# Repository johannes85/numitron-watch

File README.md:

Numitron Geekwatch
==============

See: http://www.domestichacks.info/projekte/numitron-geekwatch-armbanduhr/

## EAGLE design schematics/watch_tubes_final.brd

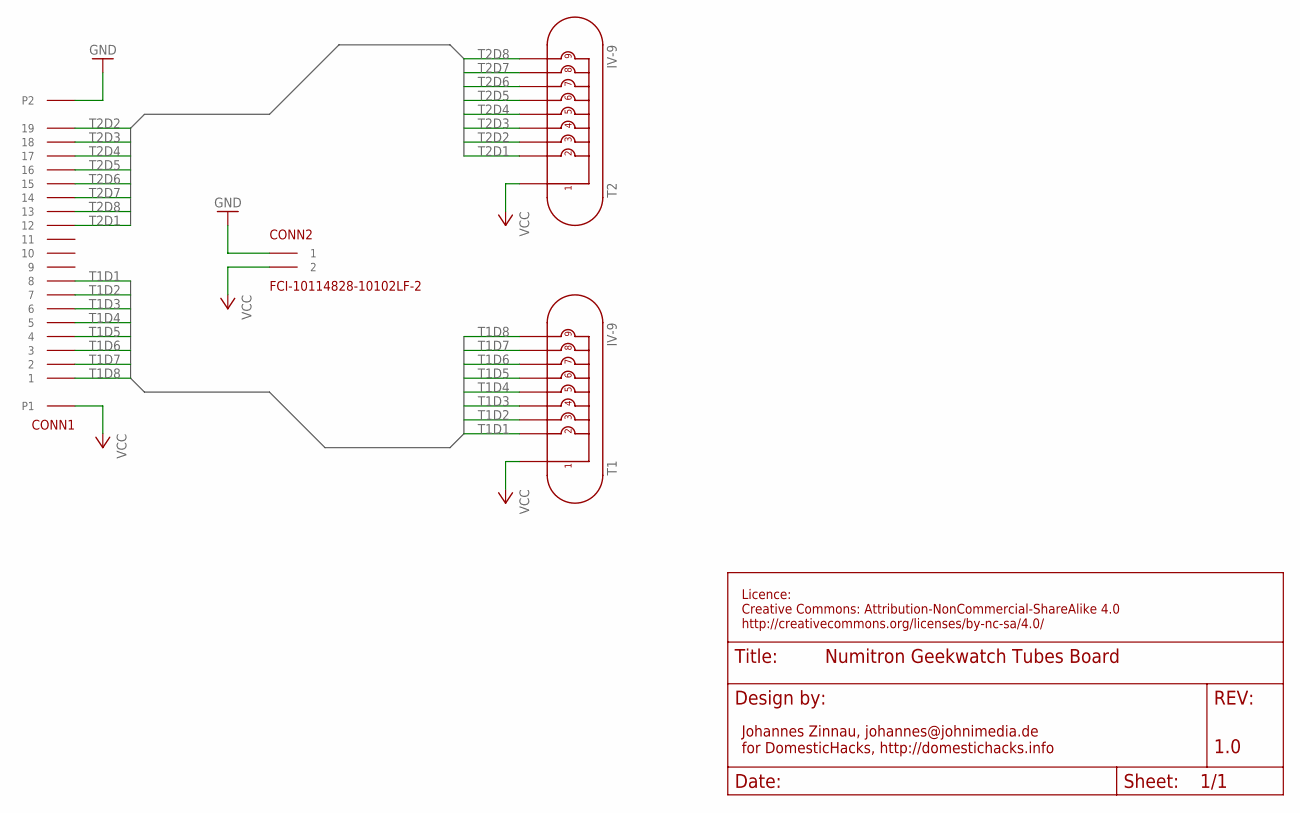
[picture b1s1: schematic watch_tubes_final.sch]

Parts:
CONN1: PCBMOUNT-20SECOND; PCBMOUNT-VERTICAL-20-2
CONN2: FCI-10114828-10102LF-2
T1, T2: IV-9

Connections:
GND: CONN1.P2, CONN2.1
T1D1: CONN1.8, T1.2
T1D2: CONN1.7, T1.3
T1D3: CONN1.6, T1.4
T1D4: CONN1.5, T1.5
T1D5: CONN1.4, T1.6
T1D6: CONN1.3, T1.7
T1D7: CONN1.2, T1.8
T1D8: CONN1.1, T1.9
T2D1: CONN1.12, T2.2
T2D2: CONN1.19, T2.3
T2D3: CONN1.18, T2.4
T2D4: CONN1.17, T2.5
T2D5: CONN1.16, T2.6
T2D6: CONN1.15, T2.7
T2D7: CONN1.14, T2.8
T2D8: CONN1.13, T2.9
VCC: CONN1.P1, CONN2.2, T1.1, T2.1

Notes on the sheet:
Licence: Creative Commons: Attribution-NonCommercial-ShareAlike 4.0 http://creativecommons.org/licenses/by-nc-sa/4.0/
Johannes Zinnau, johannes@johnimedia.de for DomesticHacks, http://domestichacks.info
1.0

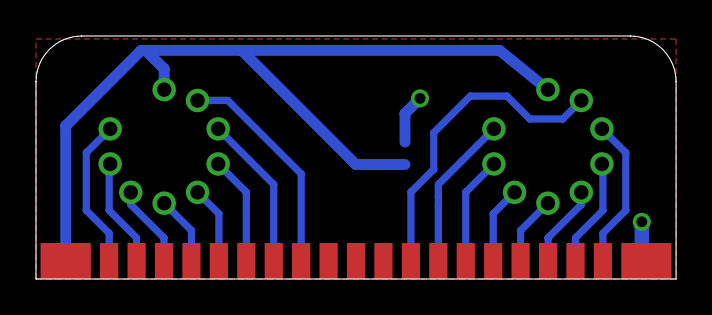
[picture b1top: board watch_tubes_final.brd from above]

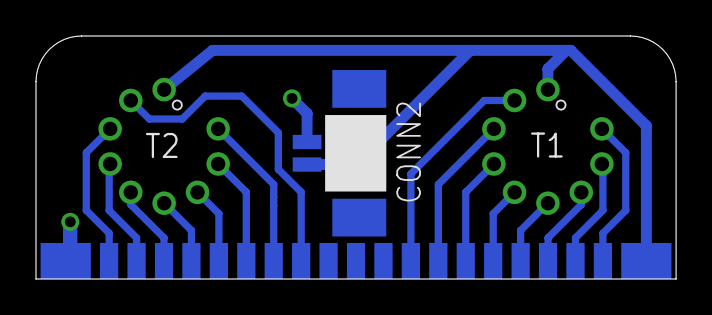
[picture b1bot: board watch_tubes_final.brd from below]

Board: 2 copper layers, 35.6 x 13.5 mm, 4 parts (4 on the bottom side), 18 nets.

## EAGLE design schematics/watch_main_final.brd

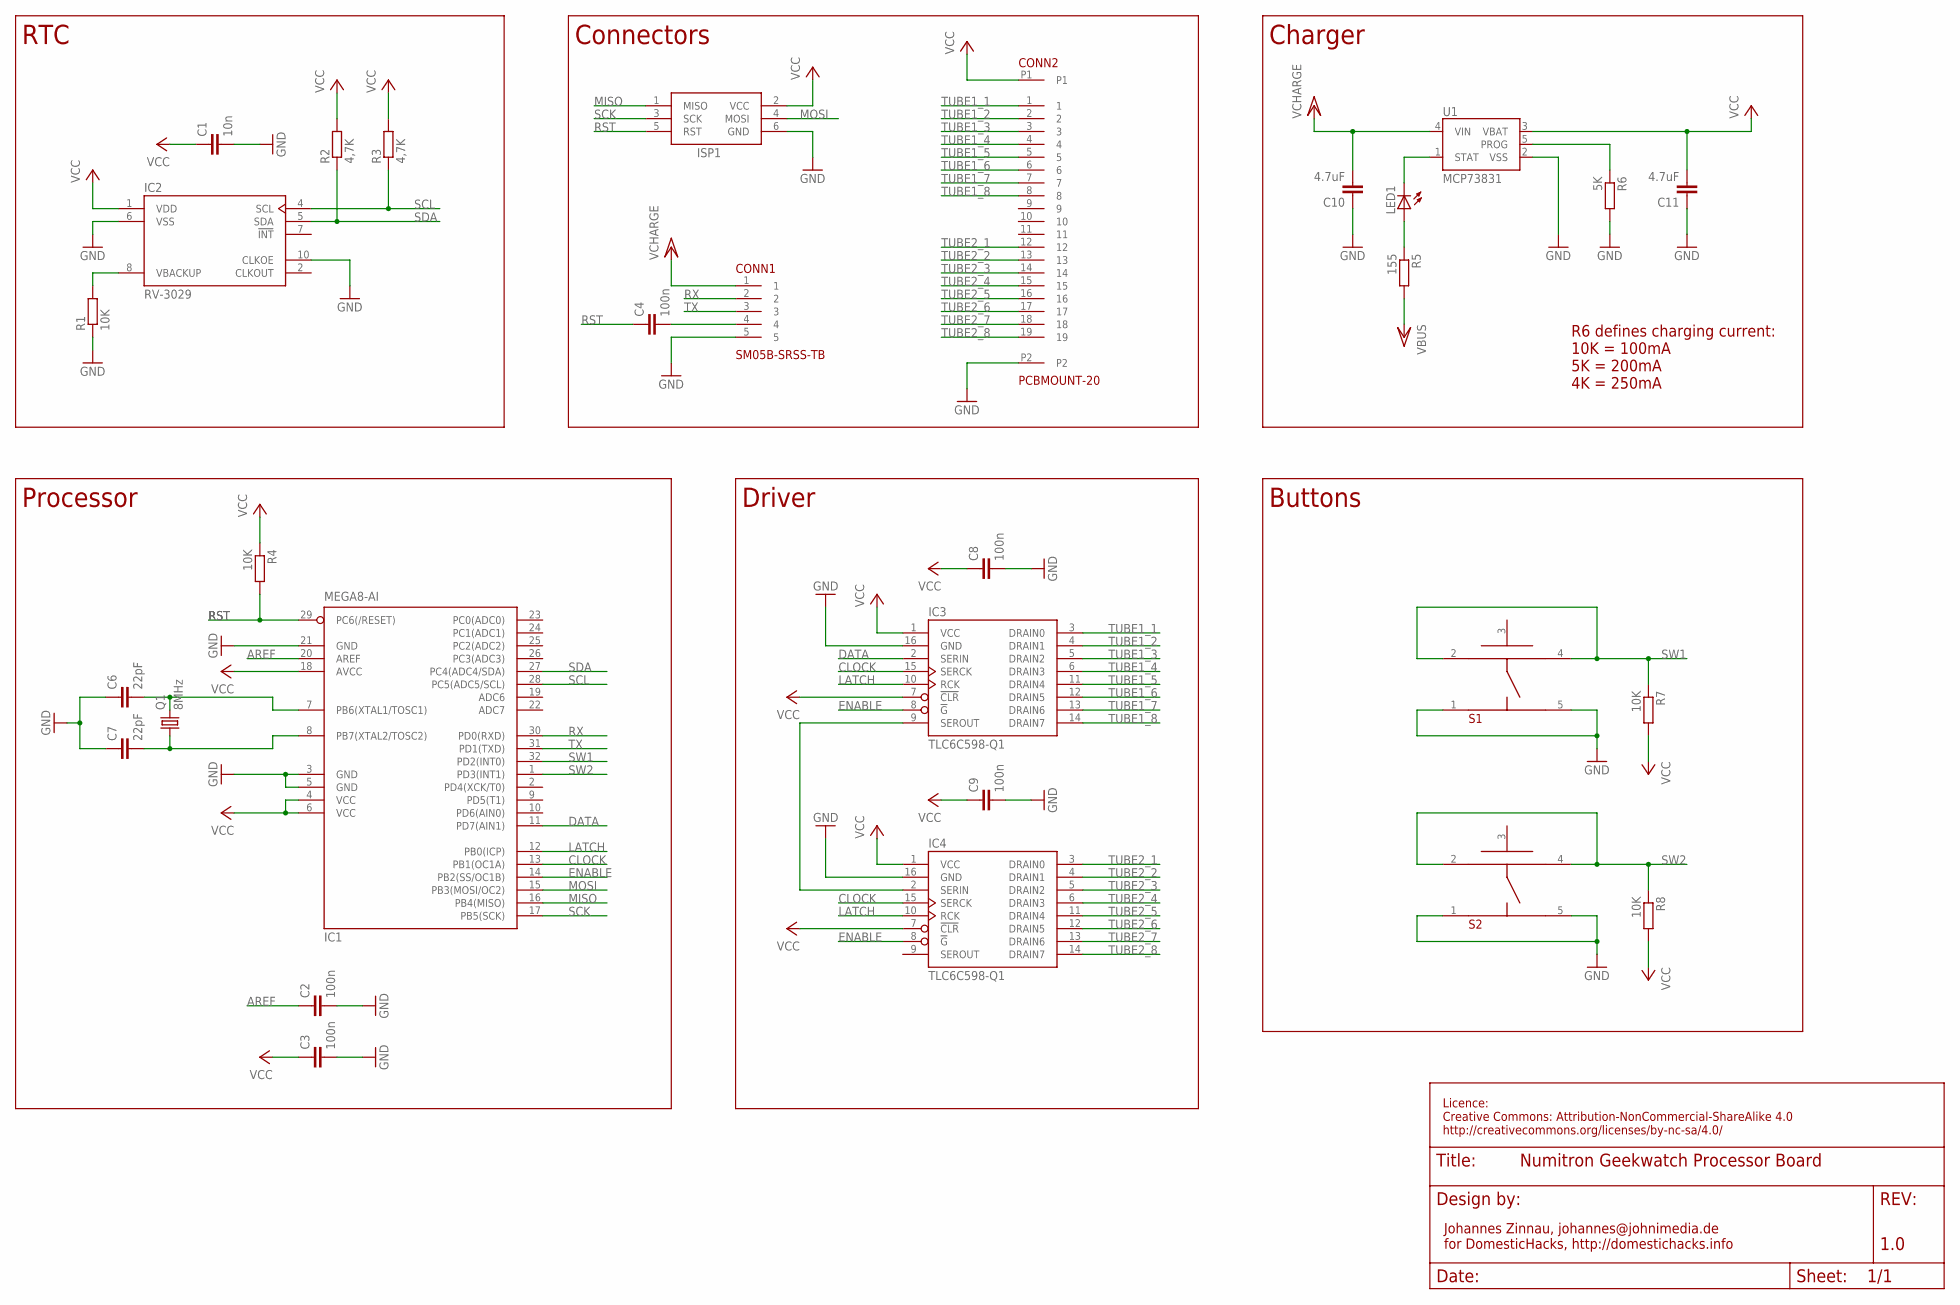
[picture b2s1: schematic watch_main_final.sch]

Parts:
C1: 10n; C0603
C2, C3, C4, C8, C9: 100n; C0603
C6, C7: 22pF; C0603
C10, C11: 4.7uF; C0603
CONN1: SM05B-SRSS-TB; JST-SR-SIDE-5
CONN2: PCBMOUNT-20; PCBMOUNT-VERTICAL-20
IC1: MEGA8-AI; TQFP32-08
IC2: RV-3029; RV-3029-C2
IC3, IC4: TLC6C598-Q1; TSSOP-16
ISP1: AVRISP-6; AVRISP
LED1: HSMA/C/L-C120FLIPPED; LED-0603-SIDE-FLIPPED
Q1: 8MHz; MQ
R1, R4, R7, R8: 10K; R0603
R2, R3: 4,7K; R0603
R5: 155; R0603
R6: 5K; R0603
S1, S2: KMSXXXG; C&K-KMS-SWITCH
U1: MCP73831; SOT23-5

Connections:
AREF: C2.1, IC1.20 (AREF)
CLOCK: IC1.13 (PB1(OC1A)), IC3.15 (SERCK), IC4.15 (SERCK)
DATA: IC1.11 (PD7(AIN1)), IC3.2 (SERIN)
ENABLE: IC1.14 (PB2(SS/OC1B)), IC3.8 (!G), IC4.8 (!G)
GND: C1.2, C2.2, C3.2, C6.1, C7.1, C8.2, C9.2, C10.1, C11.1, CONN1.5, CONN2.P2, IC1.3 (GND), IC1.5 (GND), IC1.21 (GND), IC2.6 (VSS), IC2.10 (CLKOE), IC3.16 (GND), IC4.16 (GND), ISP1.6 (GND), R1.1, R6.2, S1.1, S1.5, S2.1, S2.5, U1.2 (VSS)
LATCH: IC1.12 (PB0(ICP)), IC3.10 (RCK), IC4.10 (RCK)
MISO: IC1.16 (PB4(MISO)), ISP1.1 (MISO)
MOSI: IC1.15 (PB3(MOSI/OC2)), ISP1.4 (MOSI)
unnamed: IC2.8 (VBACKUP), R1.2
unnamed: IC3.9 (SEROUT), IC4.2 (SERIN)
unnamed: C6.2, IC1.7 (PB6(XTAL1/TOSC1)), Q1.P3 (2)
unnamed: C7.2, IC1.8 (PB7(XTAL2/TOSC2)), Q1.P1 (1)
unnamed: LED1.C, U1.1 (STAT)
unnamed: LED1.A, R5.1
unnamed: R6.1, U1.5 (PROG)
unnamed: C4.2, CONN1.4
RST: C4.1, IC1.29 (PC6(/RESET)), ISP1.5 (RST), R4.2
RX: CONN1.2, IC1.30 (PD0(RXD))
SCK: IC1.17 (PB5(SCK)), ISP1.3 (SCK)
SCL: IC1.28 (PC5(ADC5/SCL)), IC2.4 (SCL), R3.1
SDA: IC1.27 (PC4(ADC4/SDA)), IC2.5 (SDA), R2.1
SW1: IC1.32 (PD2(INT0)), R7.1, S1.2, S1.4
SW2: IC1.1 (PD3(INT1)), R8.1, S2.2, S2.4
TUBE1_1: CONN2.1, IC3.3 (DRAIN0)
TUBE1_2: CONN2.2, IC3.4 (DRAIN1)
TUBE1_3: CONN2.3, IC3.5 (DRAIN2)
TUBE1_4: CONN2.4, IC3.6 (DRAIN3)
TUBE1_5: CONN2.5, IC3.11 (DRAIN4)
TUBE1_6: CONN2.6, IC3.12 (DRAIN5)
TUBE1_7: CONN2.7, IC3.13 (DRAIN6)
TUBE1_8: CONN2.8, IC3.14 (DRAIN7)
TUBE2_1: CONN2.12, IC4.3 (DRAIN0)
TUBE2_2: CONN2.13, IC4.4 (DRAIN1)
TUBE2_3: CONN2.14, IC4.5 (DRAIN2)
TUBE2_4: CONN2.15, IC4.6 (DRAIN3)
TUBE2_5: CONN2.16, IC4.11 (DRAIN4)
TUBE2_6: CONN2.17, IC4.12 (DRAIN5)
TUBE2_7: CONN2.18, IC4.13 (DRAIN6)
TUBE2_8: CONN2.19, IC4.14 (DRAIN7)
TX: CONN1.3, IC1.31 (PD1(TXD))
VCC: C1.1, C3.1, C8.1, C9.1, C11.2, CONN2.P1, IC1.4 (VCC), IC1.6 (VCC), IC1.18 (AVCC), IC2.1 (VDD), IC3.1 (VCC), IC3.7 (!CLR), IC4.1 (VCC), IC4.7 (!CLR), ISP1.2 (VCC), R2.2, R3.2, R4.1, R7.2, R8.2, U1.3 (VBAT)
VCC/2: C10.2, CONN1.1, R5.2, U1.4 (VIN)

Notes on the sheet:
RTC
Processor
Driver
Connectors
R6 defines charging current: 10K = 100mA 5K = 200mA 4K = 250mA
Charger
Buttons
Licence: Creative Commons: Attribution-NonCommercial-ShareAlike 4.0 http://creativecommons.org/licenses/by-nc-sa/4.0/
Johannes Zinnau, johannes@johnimedia.de for DomesticHacks, http://domestichacks.info
1.0

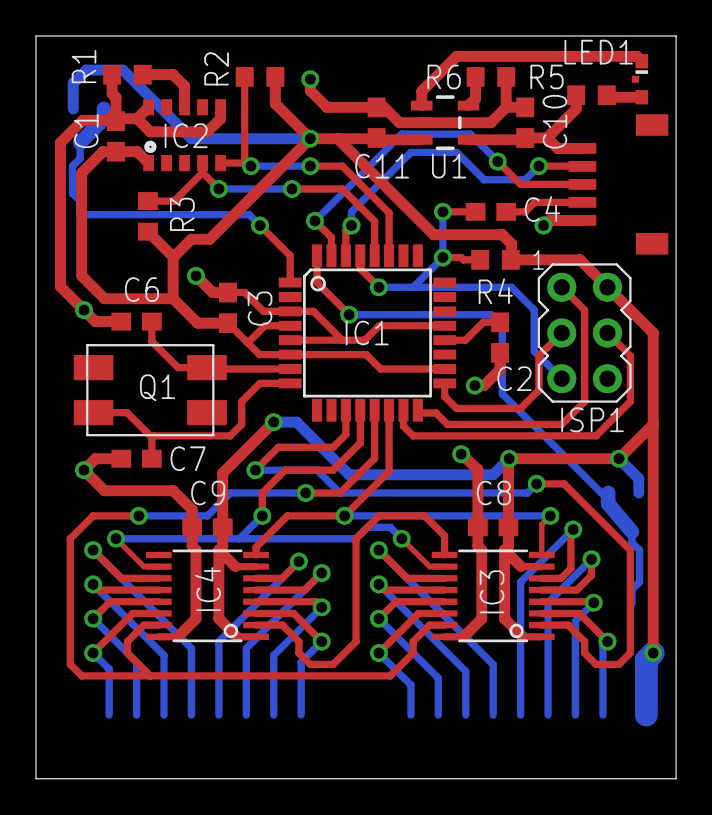
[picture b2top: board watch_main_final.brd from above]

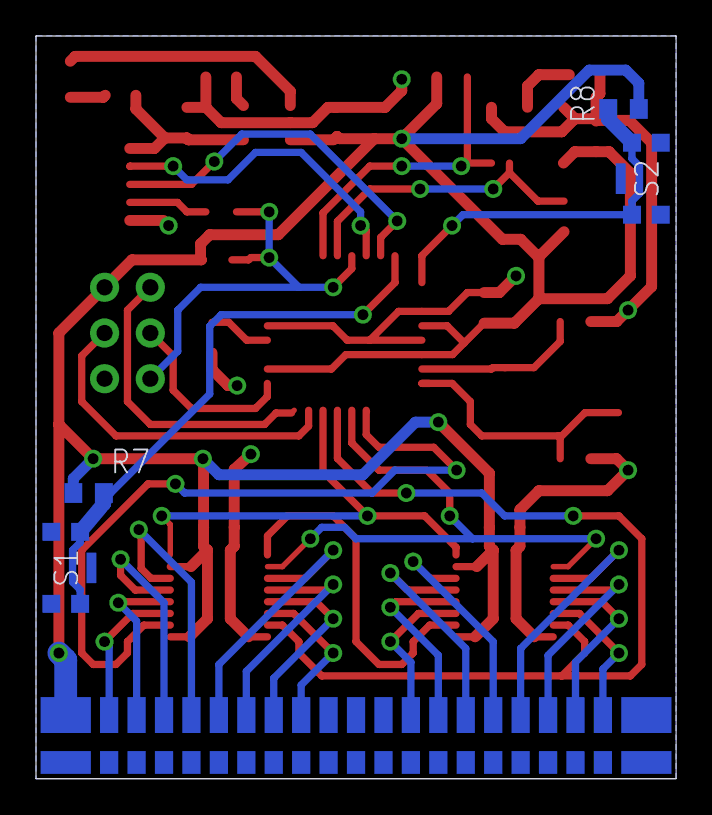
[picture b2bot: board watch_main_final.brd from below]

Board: 2 copper layers, 35.6 x 41.3 mm, 30 parts (5 on the bottom side), 42 nets.

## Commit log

2014-07-20 Initial release
2014-07-20 Added license
2015-02-12 Added TOTP screen Added UNIX timestamp calculation Added UTC offset setting

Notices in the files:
parts and their libraries:
SparkFun-PowerIC: Licensing: CC v3.0 Share-Alike You are welcome to use this library for commercial purposes.
